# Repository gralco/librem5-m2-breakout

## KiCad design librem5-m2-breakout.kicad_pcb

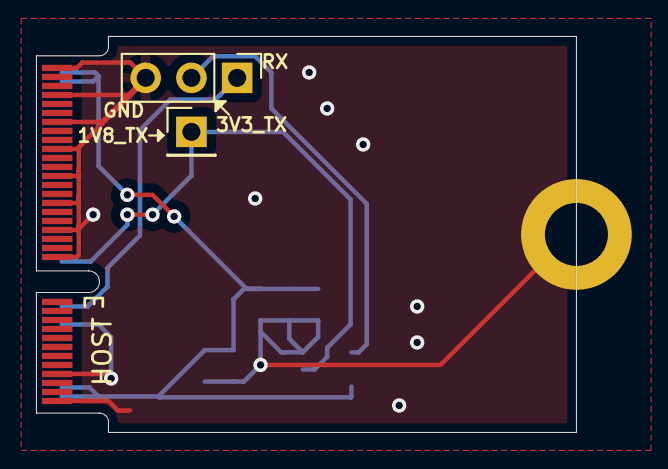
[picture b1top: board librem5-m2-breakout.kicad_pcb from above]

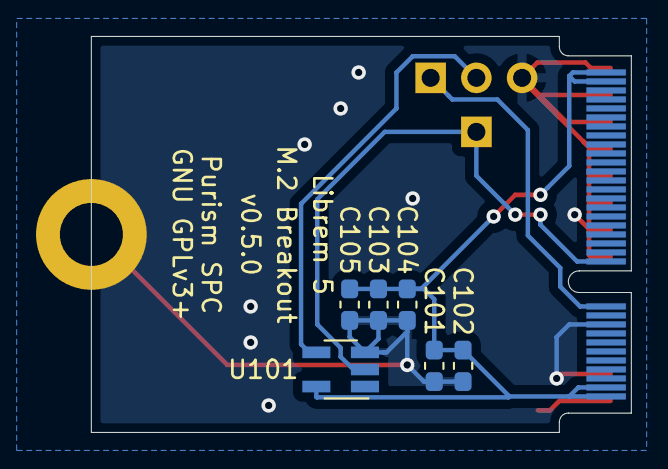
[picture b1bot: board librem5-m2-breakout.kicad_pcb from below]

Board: 2 copper layers, 30.0 x 22.0 mm, 10 parts (6 on the bottom side), 5 nets.

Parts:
C101: 1uF; C_0603_1608Metric_Pad1.05x0.95mm_HandSolder
C102, C105: 100nF; C_0603_1608Metric_Pad1.05x0.95mm_HandSolder
C103, C104: 22uF; C_0603_1608Metric_Pad1.05x0.95mm_HandSolder
H101: MountingHole_Pad; M.2_Mounting_Hole
J101: M.2_Key_E; M.2_Key_E_Gold_Fingers
J105: Conn_01x01; PinHeader_1x01_P2.54mm_Vertical
J106: Conn_01x03; PinHeader_1x03_P2.54mm_Vertical
U101: SN74LV1T34DBV; SOT-23-5_HandSoldering

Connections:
+3V3: C101.2, C102.2, C103.2, C104.2, C105.2, J101.2, J101.4, J101.72, J101.74, U101.5
/SoC_UART_RX: J101.22, J106.1
/SoC_UART_TX: J101.32, J105.1, U101.2
/SoC_UART_TX_3V3: J106.2, U101.4
GND: C101.1, C102.1, C103.1, C104.1, C105.1, H101.1, J101.1, J101.7, J101.18, J101.33, J101.39, J101.45, J101.51, J101.57, J101.63, J101.69, J101.75, J106.3, U101.3

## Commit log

2020-01-13 Add 2-layer board that's only for UART4
2020-02-02 Update the BOM to correctly reflect that the microUSB receptacle is the THT vertical Wurth Elektronik 614105150721
2022-08-19 Make it so that the back side of the M.2 mounting hole has a solid copper flood attached to it
    Add some stitching vias, joining the top and bottom ground planes in a
    few more spots.

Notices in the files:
librem5-m2-breakout.kicad_pcb:
GNU GPLv3+
